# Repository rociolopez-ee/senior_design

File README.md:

# 🎧 MultiLink Portable Bluetooth Speaker - KiCad Design Files

This repository contains the full **KiCad project files** for the Multilink Portable Bluetooth Speaker designed by **Team 5 – Synergy Electronics** as part of the **Senior Design Capstone at San Diego State University (EE/COMPE 492)**.

## 📦 What’s Inside

This repository includes:
- **Schematic files** for the main and secondary speaker PCBs
- **PCB layout** for a custom 4-layer board
- **Bill of Materials (BOM)**
- **Gerber files** for fabrication
- **Custom footprints and symbols**

> 🎯 These designs were used to build and test a working multilink Bluetooth audio system using STM32/ATmega microcontrollers, BM83 Bluetooth modules, and a custom audio amplification chain.

---

## 🔧 Project Overview

The MultiLink Portable Bluetooth Speaker was designed to:
- Support **multi-speaker synchronized audio** via BM83 Bluetooth modules (host/embedded mode)
- Include **custom power amplifier** and **op-amp gain stages** (LF353 + discrete PA)
- Be powered by **20V DeWalt tool batteries**
- Use **custom enclosures** built from birch wood and plexiglass

🧠 PCB design and layout were done using KiCad 7 and included thermal planning, decoupling, and signal integrity improvements based on EMI/grounding test results.

---

## 🧪 PCB Design Highlights

- ✍️ **4-layer PCB**, designed for both signal integrity and ease of debugging
- 🔁 **Op-amp gain stage** (V=4.3) before power amplifier (V=2.2) for total gain ≈ 9.4 V/V
- 💡 **BM83 Bluetooth module** with UART interface to microcontroller
- 🔌 **Volume, pairing, and power buttons** routed via microcontroller
- 🌡️ **Thermal design** included heatsinks for voltage regulator and amplifier transistors
- 🛠️ Manual fixes applied to final board: jumper wires and capacitor routing corrections

---
🎥 Project Demo: [YouTube Video](https://youtube.com/shorts/QWg84WqX6ao?feature=share)
---

## 👥 Team Members

- **Rocio Lopez** – Project Manager, Lead PCB Designer  
- **Po-Jui Su** – Power Systems Engineer  
- **Ryan Minsky** – Firmware Engineer ([@rminsky42](https://github.com/rminsky42))
- **Giuseppe Aiello** – Enclosure Designer, Secondary PCB Assembler  
- **Jeffrey Chin** – Project Coordinator  

---

## ⚠️ Disclaimer

This repository contains files for educational and demonstration purposes. No commercial use is authorized.

---

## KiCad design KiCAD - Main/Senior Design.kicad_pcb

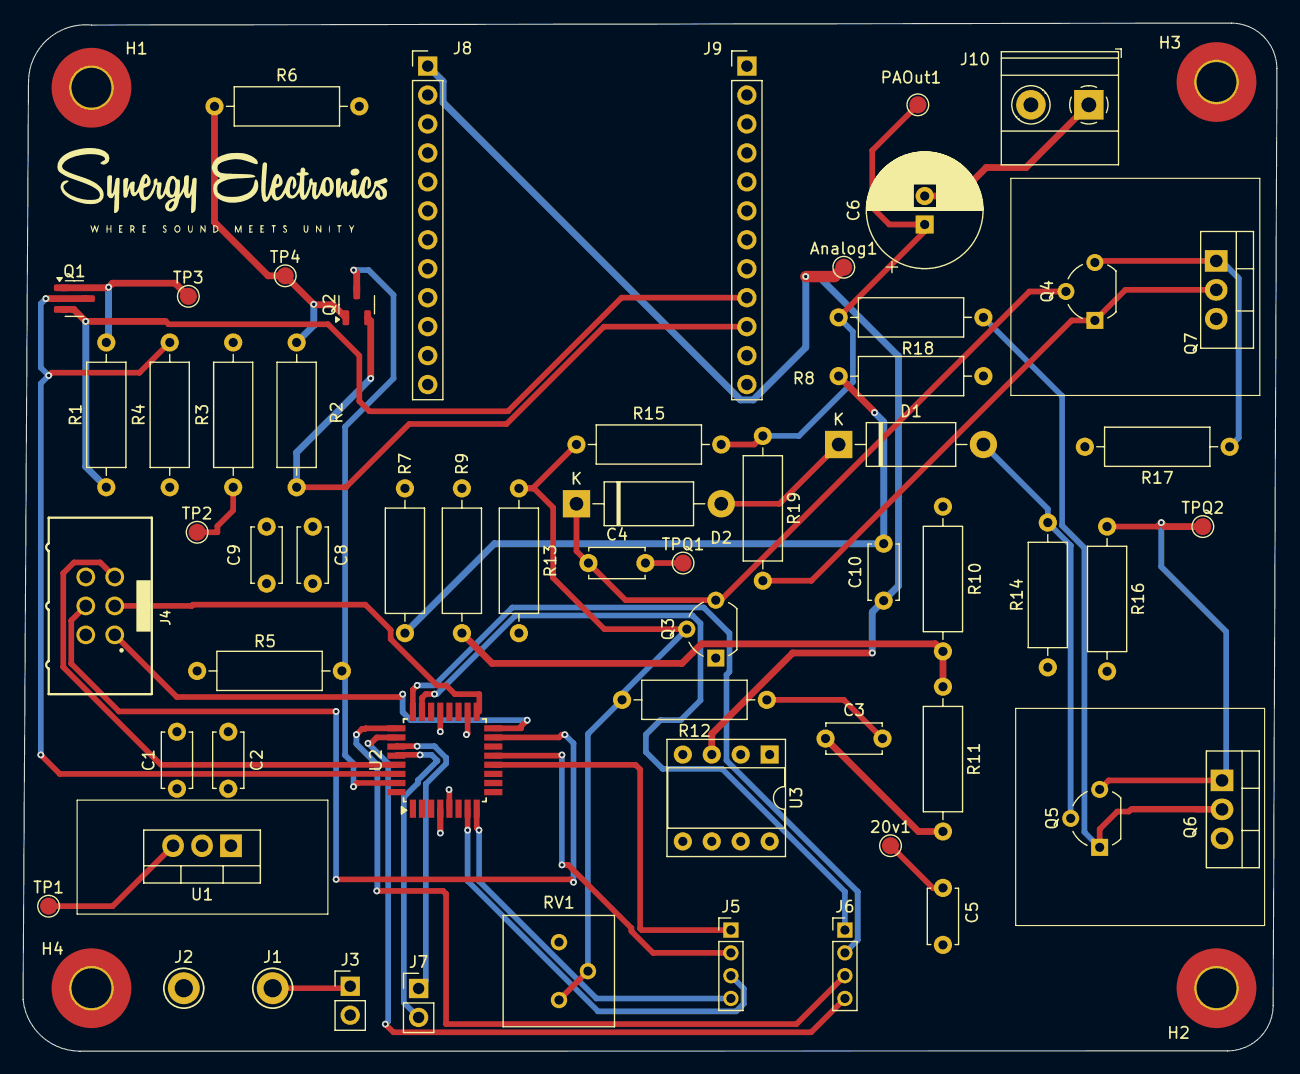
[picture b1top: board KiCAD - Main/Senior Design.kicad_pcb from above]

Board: 4 copper layers, 110.0 x 90.2 mm, 64 parts (0 on the bottom side), 38 nets.

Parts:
20v1: TestPoint; TestPoint_Pad_D1.5mm
Analog1: TestPoint; TestPoint_Pad_D1.5mm
C1: 0.33uF; C_Disc_D4.7mm_W2.5mm_P5.00mm
C2: 0.1uF; C_Disc_D4.7mm_W2.5mm_P5.00mm
C3, C8, C10: 1uF; C_Disc_D4.7mm_W2.5mm_P5.00mm
C4: 1nF; C_Disc_D4.7mm_W2.5mm_P5.00mm
C5: 0.22uF; C_Disc_D4.7mm_W2.5mm_P5.00mm
C6: 1000uF; CP_Radial_D10.0mm_P2.50mm
C9: .1uF; C_Disc_D4.7mm_W2.5mm_P5.00mm
D1, D2: 1N4148; D_DO-15_P12.70mm_Horizontal
H1, H2, H3, H4: MountingHole_Pad; MountingHole_3.5mm_Pad_TopBottom
J1, J2: Conn_01x01; TestPoint_Keystone_5010-5014_Multipurpose
J3, J7: Conn_01x02; PinHeader_1x02_P2.54mm_Vertical
J4: 6120XX21621_61200621621; 61200621621
J5, J6: Conn_01x04; PinHeader_1x04_P2.00mm_Vertical
J8, J9: Conn_01x12; PinHeader_1x12_P2.54mm_Vertical
J10: Screw_Terminal_01x02; TerminalBlock_Phoenix_MKDS-1,5-2-5.08_1x02_P5.08mm_Horizont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
PAOut1: TestPoint; TestPoint_Pad_D1.5mm
Q1, Q2: BSS138; SOT-23-3
Q3, Q5: 2N3904; TO-92_Wide
Q4: 2N3906; TO-92_Wide
Q6: D45H8; TO-220-3_Vertical
Q7: D44H8; TO-220-3_Vertical
R1, R2, R4, R5, R6, R7, R8, R16, R17: 10k; R_Axial_DIN0309_L9.0mm_D3.2mm_P12.70mm_Horizontal
R3: 5k; R_Axial_DIN0309_L9.0mm_D3.2mm_P12.70mm_Horizontal
R9, R10: 2k; R_Axial_DIN0309_L9.0mm_D3.2mm_P12.70mm_Horizontal
R11: 3.3k; R_Axial_DIN0309_L9.0mm_D3.2mm_P12.70mm_Horizontal
R12, R14: 4.7k; R_Axial_DIN0309_L9.0mm_D3.2mm_P12.70mm_Horizontal
R13: 1000; R_Axial_DIN0309_L9.0mm_D3.2mm_P12.70mm_Horizontal
R15: 12k; R_Axial_DIN0309_L9.0mm_D3.2mm_P12.70mm_Horizontal
R18, R19: 0.22; R_Axial_DIN0309_L9.0mm_D3.2mm_P12.70mm_Horizontal
RV1: R_Potentiometer_US; Potentiometer_Bourns_3386P_Vertical
TP1, TP2, TP3, TP4: TestPoint; TestPoint_Pad_D1.5mm
TPQ1, TPQ2: TestPoint; TestPoint_Pad_D1.5mm
U1: L78L05_TO220; TO-220-3_Vertical
U2: ATmega328PB-A; TQFP-32_7x7mm_P0.8mm
U3: LF353N; DIP-8_W7.62mm_Socket

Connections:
5VDC: C2.1, C8.1, C9.1, J4.2, J8.10, R3.1, R4.1, R5.1, R7.1, R9.1, TP2.1, U1.1 (VO), U2.4 (VCC), U2.18 (AVCC), U3.8 (V+)
20VDC: 20v1.1, C1.1, C5.1, J3.2, Q6.3 (E), R14.1, R16.2, TP1.1, U1.3 (VI)
/Microprocessor & Connectors/3_3VDC: Q1.1 (G), Q2.1 (G), R1.1, R2.1, R3.2, R6.1, TP3.1, TP4.1
/Microprocessor & Connectors/MISO: J4.1, U2.16 (PB4)
/Microprocessor & Connectors/MOSI: J4.4, U2.15 (PB3)
/Microprocessor & Connectors/Pair_LED_O: J7.1, U2.27 (PC4)
/Microprocessor & Connectors/Pair_btn_I: J5.3, U2.7 (XTAL1/PB6)
/Microprocessor & Connectors/Pair_btn_O: J5.4, U2.8 (XTAL2/PB7)
/Microprocessor & Connectors/Power_LED_O: J7.2, U2.28 (PC5)
/Microprocessor & Connectors/Power_btn_I: J5.1, U2.12 (PB0)
/Microprocessor & Connectors/Power_btn_O: J5.2, U2.13 (PB1)
/Microprocessor & Connectors/RESET: J4.5, U2.29 (~RESET/PC6)
/Microprocessor & Connectors/RX-I: J9.9, Q1.2 (S), R1.2
/Microprocessor & Connectors/RX-O: Q1.3 (D), R4.2, U2.30 (PD0)
/Microprocessor & Connectors/SCK: J4.3, U2.17 (PB5)
/Microprocessor & Connectors/TX-I: J9.10, Q2.2 (S), R2.2
/Microprocessor & Connectors/TX-O: Q2.3 (D), R5.2, U2.31 (PD1)
/Microprocessor & Connectors/Volume_D_btn_I: J6.1, U2.23 (PC0)
/Microprocessor & Connectors/Volume_D_btn_O: J6.2, U2.24 (PC1)
/Microprocessor & Connectors/Volume_U_btn_I: J6.3, U2.25 (PC2)
/Microprocessor & Connectors/Volume_U_btn_O: J6.4, U2.26 (PC3)
Analog Signal: Analog1.1, C10.1, J8.1, U3.3 (POSA)
GND: C1.2, C2.2, C4.2, C5.2, C8.2, C9.2, H1.1, H2.1, H3.1, H4.1, J2.1, J4.6, J8.7, J9.1, J10.2, Q3.1 (E), Q7.3 (E), R6.2, R8.2, R10.2, R13.2, R17.2, RV1.3, TPQ1.1, U1.2 (GND), U2.5 (GND), U2.21 (GND), U3.4 (V-)
unnamed: C3.1, R11.2
unnamed: C3.2, R12.1
unnamed: C6.1, PAOut1.1, R15.2, R18.2, R19.1
unnamed: D1.2 (A), Q5.2 (B), R14.2
unnamed: D1.1 (K), D2.2 (A)
unnamed: C4.1, D2.1 (K), Q3.3 (C), Q4.2 (B)
unnamed: J1.1, J3.1
unnamed: C6.2, J10.1
unnamed: Q3.2 (B), R12.2, R13.1, R15.1, RV1.1, RV1.2
unnamed: Q4.3 (C), Q7.1 (B), R17.1
unnamed: Q4.1 (E), Q7.2 (C), R19.2
unnamed: Q5.3 (C), Q6.1 (B), R16.1, TPQ2.1
unnamed: Q5.1 (E), Q6.2 (C), R18.1
unnamed: C10.2, R7.2, R8.1
unnamed: R9.2, R10.1, R11.1

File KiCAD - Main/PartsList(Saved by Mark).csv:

Reference,Value,Datasheet,Footprint,Qty,DNP
"20v1,Analog1,Audio1,Audio2,PAOut1,RX1,TP1,TP2,TP3,TP4,TPQ1,TPQ2,TX1",TestPoint,~,-- mixed values --,13,
C1,0.33uF,~,Capacitor_THT:C_Disc_D4.7mm_W2.5mm_P5.00mm,1,
C2,0.1uF,~,Capacitor_THT:C_Disc_D4.7mm_W2.5mm_P5.00mm,1,
"C3,C7,C8",1uF,~,Capacitor_THT:C_Disc_D4.7mm_W2.5mm_P5.00mm,3,
C4,1nF,~,Capacitor_THT:C_Disc_D4.7mm_W2.5mm_P5.00mm,1,
C5,0.22uF,~,Capacitor_THT:C_Disc_D4.7mm_W2.5mm_P5.00mm,1,
C6,1000uF,~,Capacitor_THT:C_Disc_D4.7mm_W2.5mm_P5.00mm,1,
C9,.1uF,~,Capacitor_THT:C_Disc_D4.7mm_W2.5mm_P5.00mm,1,
"D1,D2",1N4148,https://assets.nexperia.com/documents/data-sheet/1N4148_1N4448.pdf,Diode_THT:D_DO-15_P12.70mm_Horizontal,2,
"D3,D4",LED,~,LED_THT:LED_D3.0mm,2,
"J1,J2",Conn_01x01,~,TestPoint:TestPoint_Keystone_5010-5014_Multipurpose,2,
"J3,J7",Conn_01x02,~,Connector_PinHeader_2.54mm:PinHeader_1x02_P2.54mm_Vertical,2,
J4,6120XX21621_61200621621,,61200621621:61200621621,1,
"J5,J6",Conn_01x04,~,Connector_PinHeader_2.00mm:PinHeader_1x04_P2.00mm_Vertical,2,
"J8,J9,J11,J12",Conn_01x12,~,Connector_PinHeader_2.54mm:PinHeader_1x12_P2.54mm_Vertical,4,
J10,Screw_Terminal_01x02,~,"TerminalBlock_Phoenix:TerminalBlock_Phoenix_MKDS-1,5-2-5.08_1x02_P5.08mm_Horizontal",1,
"Q1,Q2",BSS138,https://www.onsemi.com/pub/Collateral/BSS138-D.PDF,Package_TO_SOT_SMD:SOT-23-3,2,
"Q3,Q5",2N3904,https://www.onsemi.com/pub/Collateral/2N3903-D.PDF,Package_TO_SOT_THT:TO-92_Wide,2,
Q4,2N3906,https://www.onsemi.com/pub/Collateral/2N3906-D.PDF,Package_TO_SOT_THT:TO-92_Wide,1,
Q6,2SB817,http://skory.gylcomp.hu/alkatresz/2SB817.pdf,Package_TO_SOT_THT:TO-220-3_Vertical,1,
Q7,2SD1047,http://www.st.com/resource/en/datasheet/2sd1047.pdf,Package_TO_SOT_THT:TO-220-3_Vertical,1,
"R1,R2,R4,R5,R6,R7,R8,R16,R17",10k,~,Resistor_THT:R_Axial_DIN0309_L9.0mm_D3.2mm_P12.70mm_Horizontal,9,
R3,5k,~,Resistor_THT:R_Axial_DIN0309_L9.0mm_D3.2mm_P12.70mm_Horizontal,1,
"R9,R10",2k,~,Resistor_THT:R_Axial_DIN0309_L9.0mm_D3.2mm_P12.70mm_Horizontal,2,
R11,3.3k,~,Resistor_THT:R_Axial_DIN0309_L9.0mm_D3.2mm_P12.70mm_Horizontal,1,
"R12,R14",4.7k,~,Resistor_THT:R_Axial_DIN0309_L9.0mm_D3.2mm_P12.70mm_Horizontal,2,
R13,1000,~,Resistor_THT:R_Axial_DIN0309_L9.0mm_D3.2mm_P12.70mm_Horizontal,1,
R15,12k,~,Resistor_THT:R_Axial_DIN0309_L9.0mm_D3.2mm_P12.70mm_Horizontal,1,
"R18,R19",0.22,~,Resistor_THT:R_Axial_DIN0309_L9.0mm_D3.2mm_P12.70mm_Horizontal,2,
RV1,R_Potentiometer_US,~,Potentiometer_THT:Potentiometer_Bourns_3386P_Vertical,1,
U1,L78L05_TO220,http://www.st.com/content/ccc/resource/technical/document/da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,Package_TO_SOT_THT:TO-220-3_Vertical,1,
U2,ATmega328PB-A,http://ww1.microchip.com/downloads/en/DeviceDoc/40001906C.pdf,Package_QFP:TQFP-32_7x7mm_P0.8mm,1,
U3,LF353N,https://www.ti.com/lit/ds/symlink/lf353-n.pdf,Package_DIP:DIP-8_W7.62mm_Socket,1,
U4,Microchip_BM83,https://ww1.microchip.com/downloads/aemDocuments/documents/W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,RF_Module:Microchip_BM83,1,

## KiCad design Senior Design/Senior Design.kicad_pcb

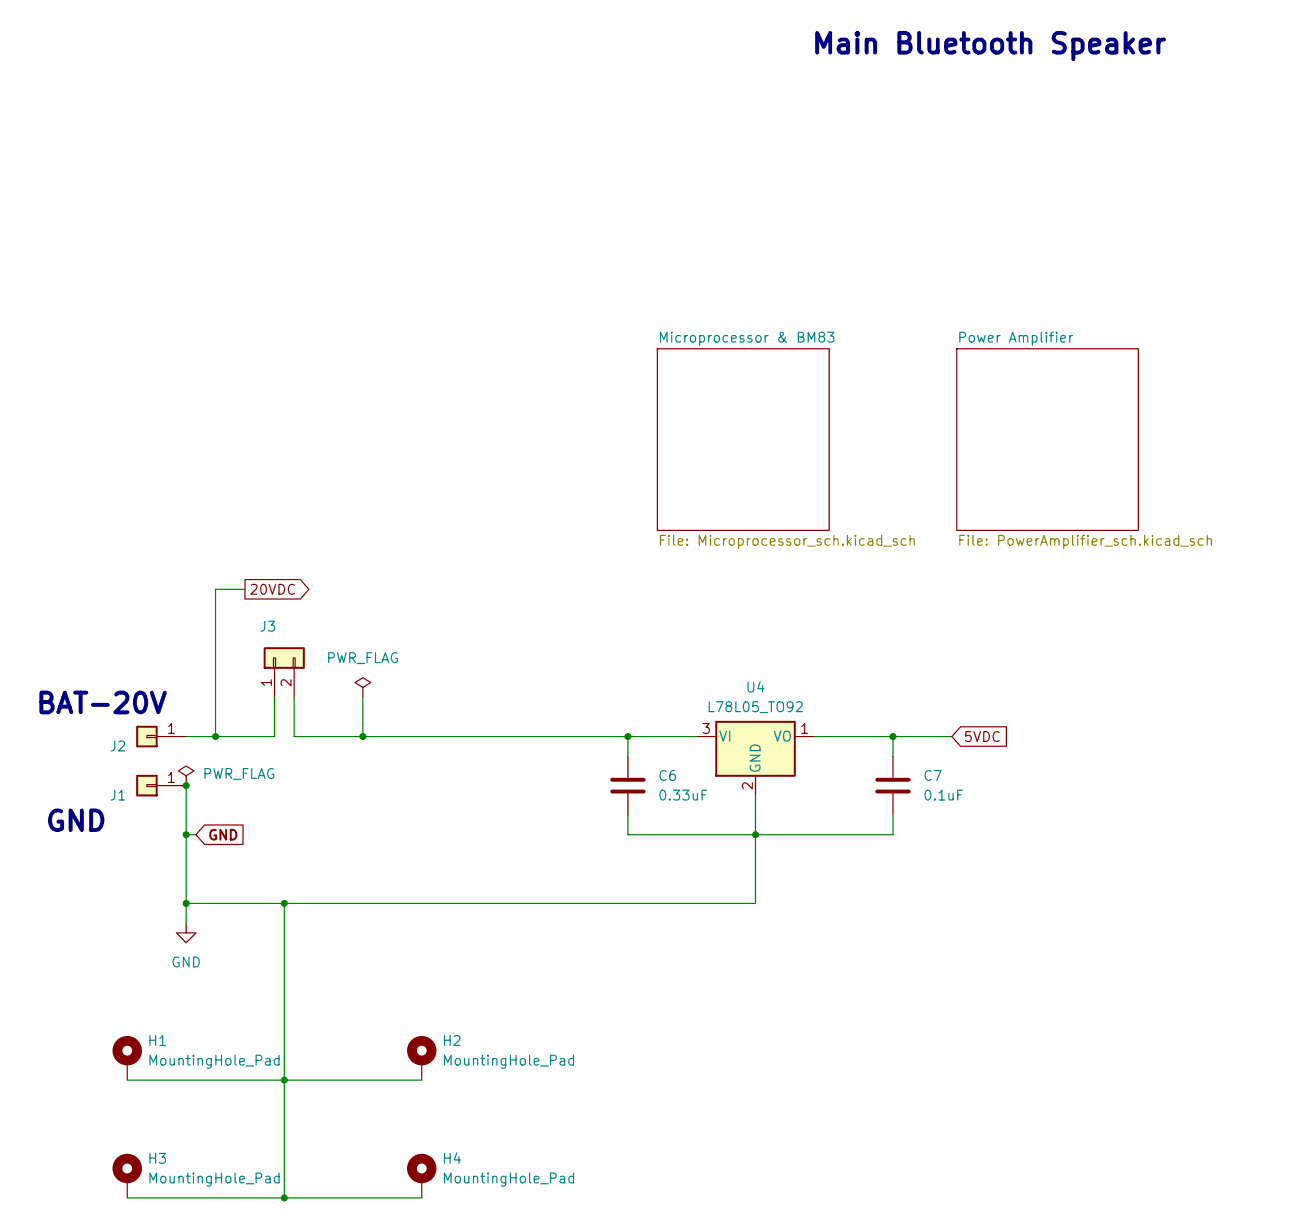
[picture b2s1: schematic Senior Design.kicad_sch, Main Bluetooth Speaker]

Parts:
C6: 0.33uF; C_Disc_D4.7mm_W2.5mm_P5.00mm
C7: 0.1uF; C_Disc_D4.7mm_W2.5mm_P5.00mm
H1, H2, H3, H4: MountingHole_Pad; MountingHole_3.5mm_Pad_TopBottom
J1, J2: Conn_01x01; TestPoint_Keystone_5010-5014_Multipurpose
J3: Conn_01x02; PinHeader_1x02_P2.54mm_Vertical
U4: L78L05_TO92; TO-92_Wide

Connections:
5VDC: C7.1, U4.1 (VO); also elsewhere on the board
20VDC: J2.1, J3.1; also elsewhere on the board
GND: C6.2, C7.2, H1.1, H2.1, H3.1, H4.1, J1.1, U4.2 (GND); also elsewhere on the board
unnamed: C6.1, J3.2, U4.3 (VI)

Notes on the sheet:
BAT-20V
GND
Main Bluetooth Speaker

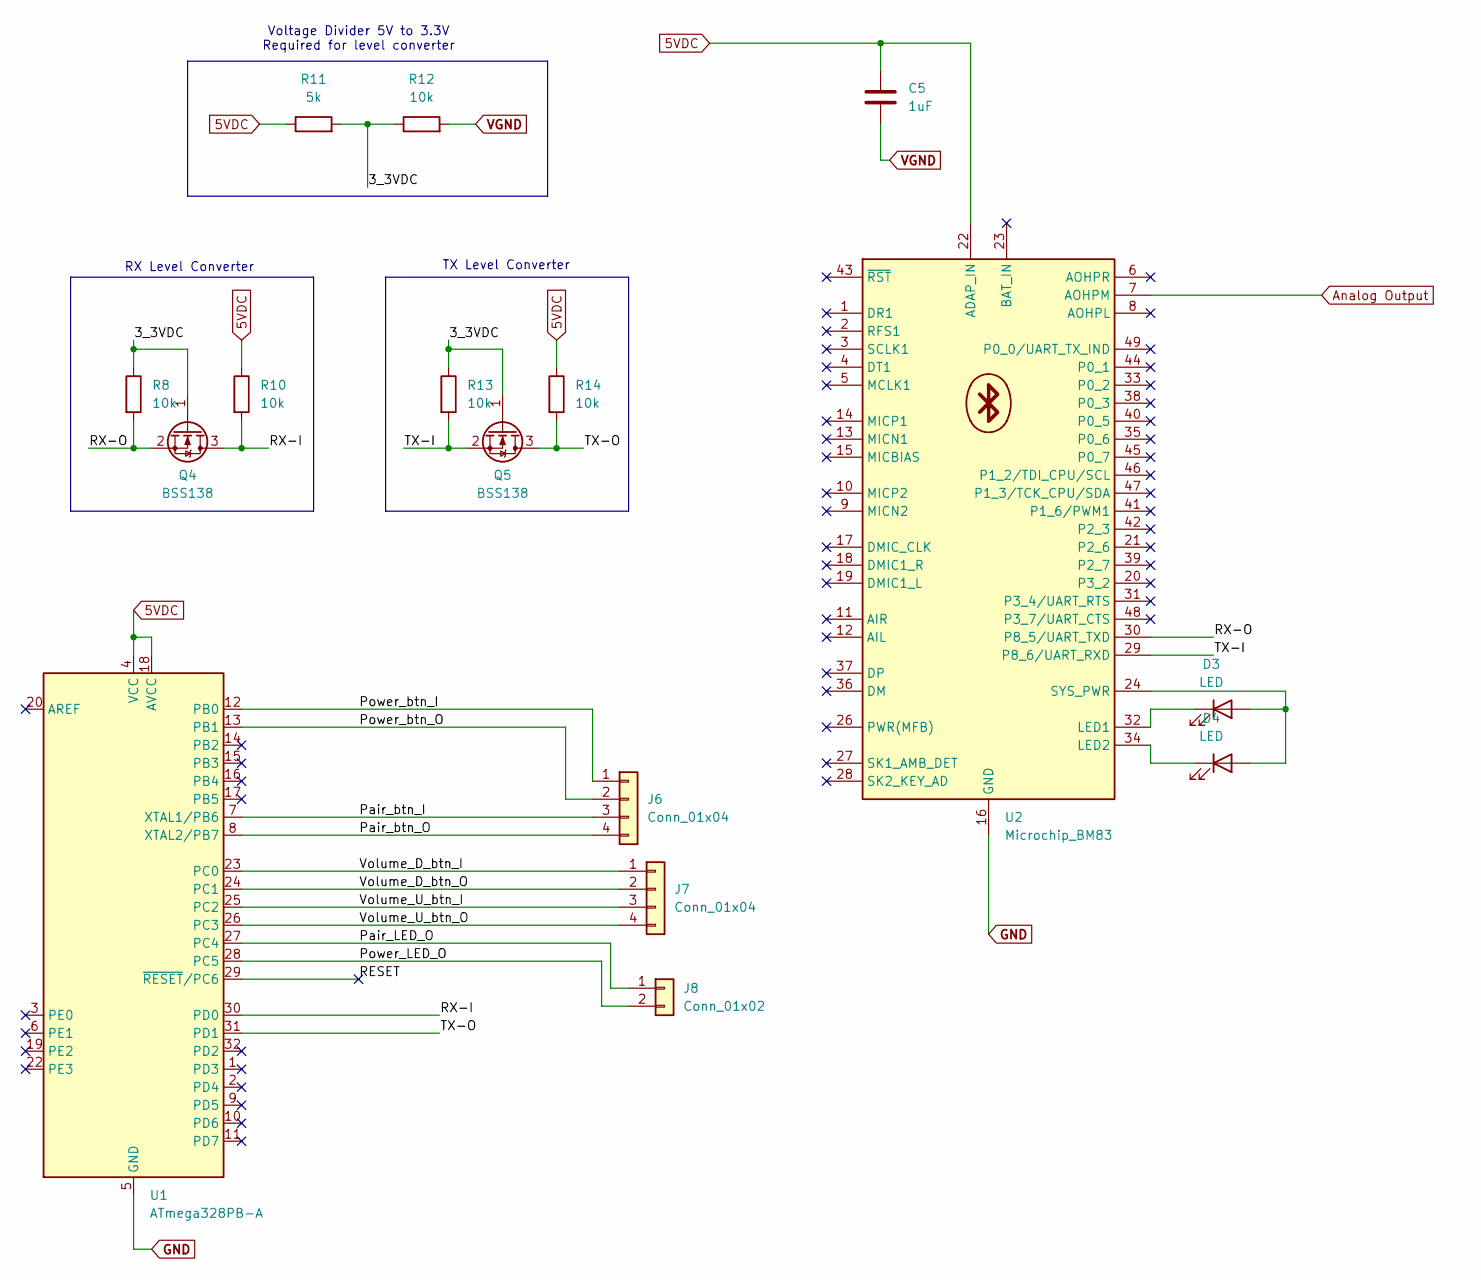
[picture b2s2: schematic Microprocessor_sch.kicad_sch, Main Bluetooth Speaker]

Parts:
C5: 1uF; C_Disc_D4.7mm_W2.5mm_P5.00mm
D3, D4: LED; LED_D5.0mm
J6, J7: Conn_01x04; PinHeader_1x04_P2.54mm_Vertical
J8: Conn_01x02; PinHeader_1x02_P2.54mm_Vertical
Q4, Q5: BSS138; SOT-23-3
R8, R10, R12, R13, R14: 10k; R_Axial_DIN0309_L9.0mm_D3.2mm_P12.70mm_Horizontal
R11: 5k; R_Axial_DIN0309_L9.0mm_D3.2mm_P12.70mm_Horizontal
U1: ATmega328PB-A; TQFP-32_7x7mm_P0.8mm
U2: Microchip_BM83

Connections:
5VDC: C5.1, R10.1, R11.1, R14.1, U1.4 (VCC), U1.18 (AVCC), U2.22 (ADAP_IN); also elsewhere on the board
/Microprocessor & BM83/3_3VDC: Q4.1 (G), Q5.1 (G), R8.1, R11.2, R12.1, R13.1
/Microprocessor & BM83/Pair_LED_O: J8.1, U1.27 (PC4)
/Microprocessor & BM83/Pair_btn_I: J6.3, U1.7 (XTAL1/PB6)
/Microprocessor & BM83/Pair_btn_O: J6.4, U1.8 (XTAL2/PB7)
/Microprocessor & BM83/Power_LED_O: J8.2, U1.28 (PC5)
/Microprocessor & BM83/Power_btn_I: J6.1, U1.12 (PB0)
/Microprocessor & BM83/Power_btn_O: J6.2, U1.13 (PB1)
/Microprocessor & BM83/RESET: U1.29 (~RESET/PC6)
/Microprocessor & BM83/RX-I: Q4.3 (D), R10.2, U1.30 (PD0)
/Microprocessor & BM83/RX-O: Q4.2 (S), R8.2, U2.30 (P8_5/UART_TXD)
/Microprocessor & BM83/TX-I: Q5.2 (S), R13.2, U2.29 (P8_6/UART_RXD)
/Microprocessor & BM83/TX-O: Q5.3 (D), R14.2, U1.31 (PD1)
/Microprocessor & BM83/Volume_D_btn_I: J7.1, U1.23 (PC0)
/Microprocessor & BM83/Volume_D_btn_O: J7.2, U1.24 (PC1)
/Microprocessor & BM83/Volume_U_btn_I: J7.3, U1.25 (PC2)
/Microprocessor & BM83/Volume_U_btn_O: J7.4, U1.26 (PC3)
Analog Output: U2.7 (AOHPM); also elsewhere on the board
GND: U1.5 (GND), U1.21 (GND), U2.16 (GND), U2.50 (GND), U2.56 (GND), U2.57 (GND); also elsewhere on the board
unnamed: D3.2 (A), D4.2 (A), U2.24 (SYS_PWR)
unnamed: D3.1 (K), U2.32 (LED1)
unnamed: D4.1 (K), U2.34 (LED2)
VGND: C5.2, R12.2

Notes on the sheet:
RX Level Converter
TX Level Converter
Voltage Divider 5V to 3.3V Required for level converter

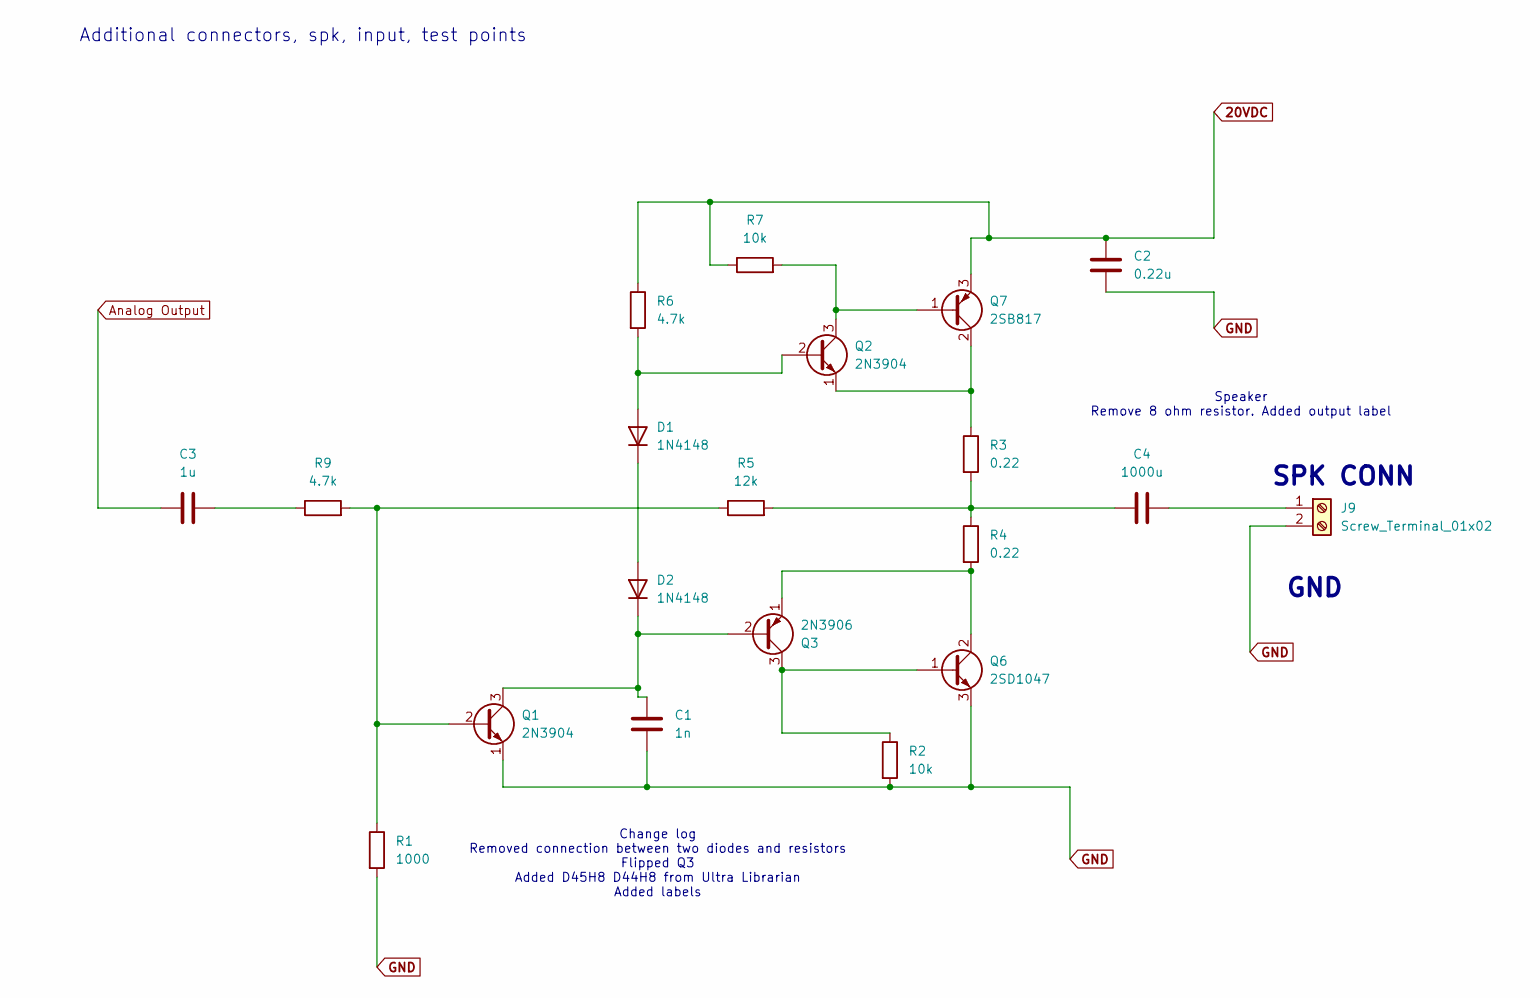
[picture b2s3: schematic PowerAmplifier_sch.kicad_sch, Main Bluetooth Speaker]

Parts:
C1: 1n; C_Disc_D4.7mm_W2.5mm_P5.00mm
C2: 0.22u; C_Disc_D4.7mm_W2.5mm_P5.00mm
C3: 1u; C_Disc_D4.7mm_W2.5mm_P5.00mm
C4: 1000u; C_Disc_D4.7mm_W2.5mm_P5.00mm
D1, D2: 1N4148; R_Axial_DIN0309_L9.0mm_D3.2mm_P12.70mm_Horizontal
J9: Screw_Terminal_01x02; TerminalBlock_Phoenix_MKDS-1,5-2-5.08_1x02_P5.08mm_Horizont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
Q1, Q2: 2N3904; TO-92_Wide
Q3: 2N3906; TO-92_Wide
Q6: 2SD1047; TO-220-3_Vertical
Q7: 2SB817; TO-220-3_Vertical
R1: 1000; R_Axial_DIN0309_L9.0mm_D3.2mm_P12.70mm_Horizontal
R2, R7: 10k; R_Axial_DIN0309_L9.0mm_D3.2mm_P12.70mm_Horizontal
R3, R4: 0.22; R_Axial_DIN0309_L9.0mm_D3.2mm_P12.70mm_Horizontal
R5: 12k; R_Axial_DIN0309_L9.0mm_D3.2mm_P12.70mm_Horizontal
R6, R9: 4.7k; R_Axial_DIN0309_L9.0mm_D3.2mm_P12.70mm_Horizontal

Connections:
20VDC: C2.1, Q7.3 (E), R6.1, R7.1; also elsewhere on the board
Analog Output: C3.1; also elsewhere on the board
GND: C1.2, C2.2, J9.2, Q1.1 (E), Q6.3 (E), R1.2, R2.2; also elsewhere on the board
unnamed: C3.2, R9.1
unnamed: C4.1, R3.2, R4.1, R5.2
unnamed: D1.2 (A), Q2.2 (B), R6.2
unnamed: D1.1 (K), D2.2 (A)
unnamed: C1.1, D2.1 (K), Q1.3 (C), Q3.2 (B)
unnamed: C4.2, J9.1
unnamed: Q1.2 (B), R1.1, R5.1, R9.2
unnamed: Q2.3 (C), Q7.1 (B), R7.2
unnamed: Q2.1 (E), Q7.2 (C), R3.1
unnamed: Q3.3 (C), Q6.1 (B), R2.1
unnamed: Q3.1 (E), Q6.2 (C), R4.2

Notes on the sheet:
Speaker Remove 8 ohm resistor. Added output label
Change log Removed connection between two diodes and resistors Flipped Q3 Added D45H8 D44H8 from Ultra Librarian Added labels
GND
SPK CONN
Additional connectors, spk, input, test points

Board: 2 copper layers, 47 parts (0 on the bottom side), 35 nets, no tracks yet.

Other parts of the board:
U3: L78L05_SO8; TO-92_Wide

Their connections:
5VDC: U3.1 (OUT); also elsewhere on the board
GND: U3.2 (GND), U3.3 (GND); also elsewhere on the board

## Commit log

2024-09-23 KiCAD files
    Files with changes up to 9/23/24, I showed Professor Dorr the schematic and he mentioned L78L05 might need to be updated to support higher current for both BM83 and Atmega, non of the Atmel Ice schem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
2025-08-19 Add files via upload
    Final Rev of PCB
